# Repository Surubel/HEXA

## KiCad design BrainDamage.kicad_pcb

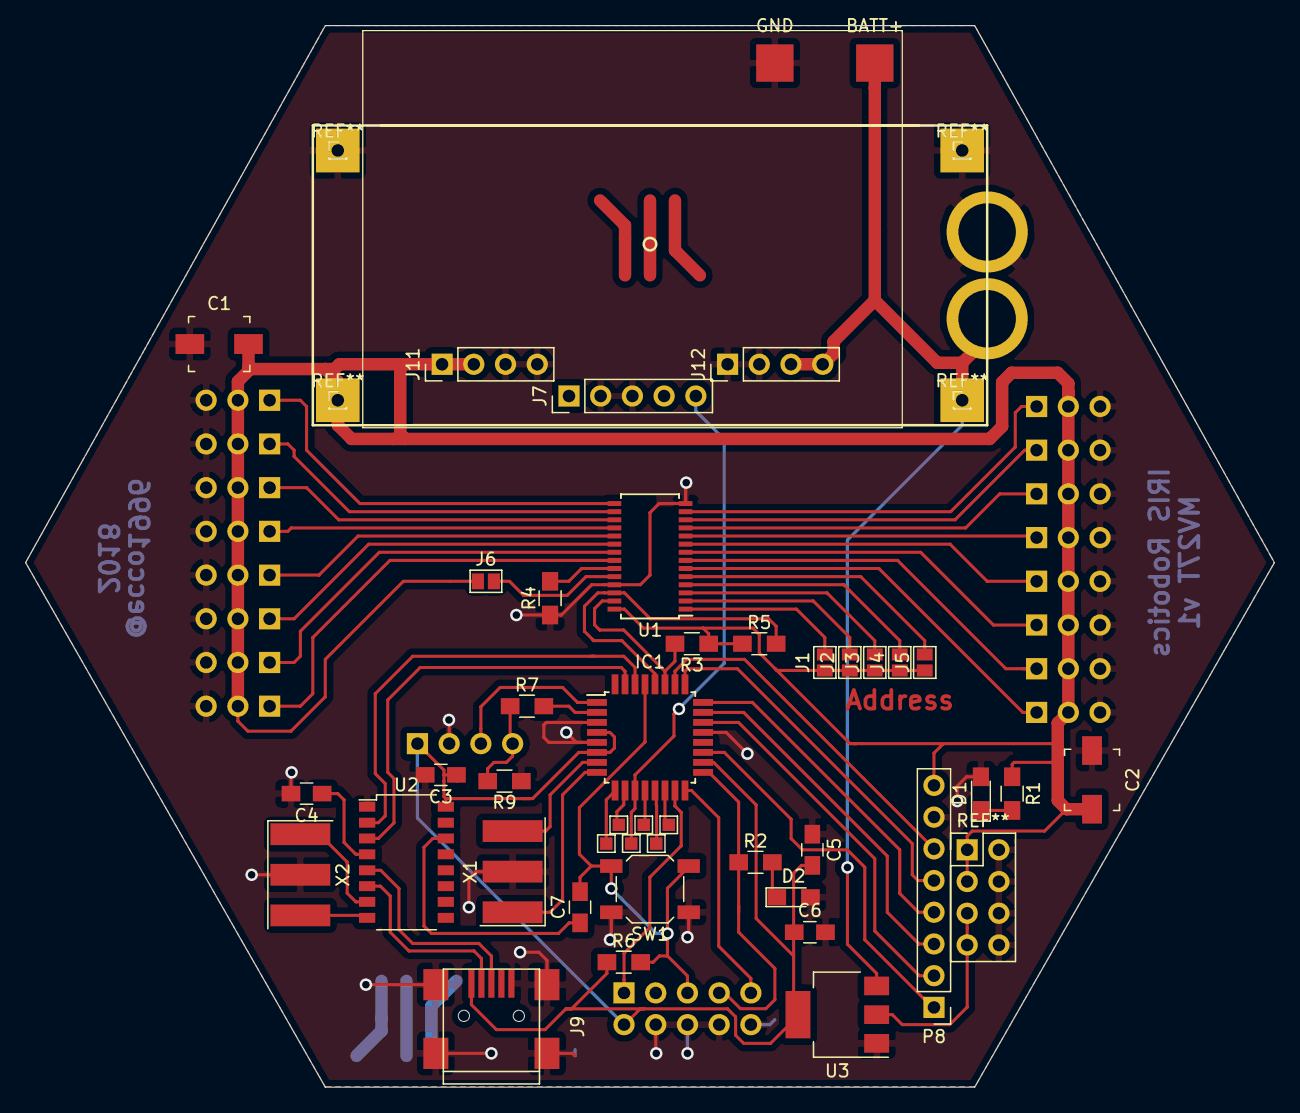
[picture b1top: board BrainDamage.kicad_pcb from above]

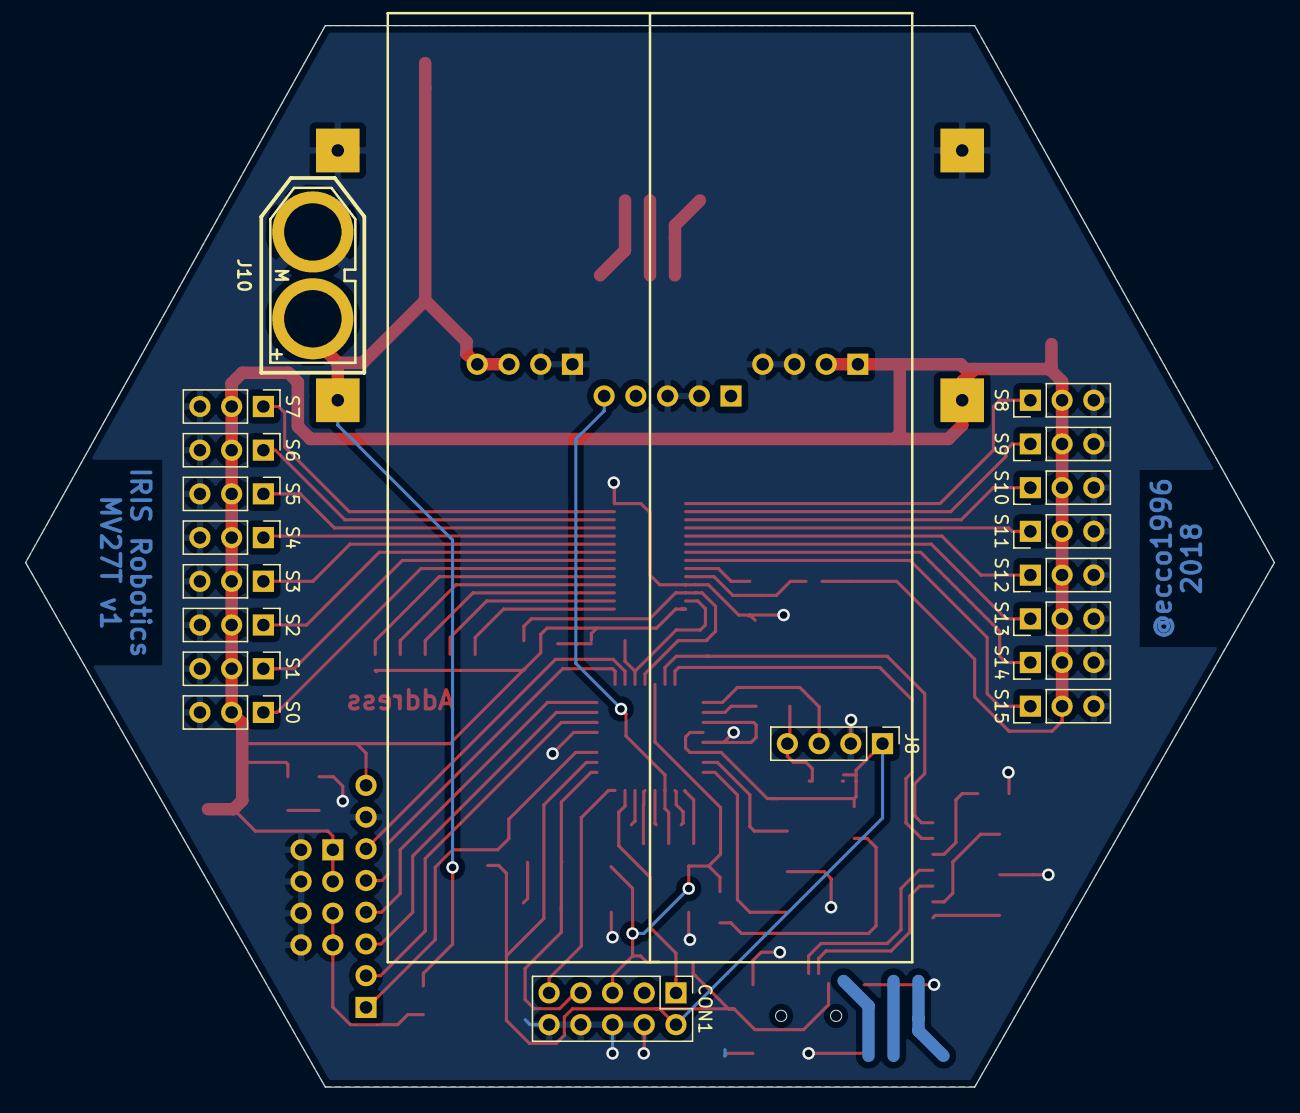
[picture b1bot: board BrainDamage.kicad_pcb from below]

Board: 2 copper layers, 100.0 x 85.0 mm, 56 parts (19 on the bottom side), 54 nets.

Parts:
BATT+: Measurement_Point_Square-SMD-Pad_Big
C1, C2: C; C_Trimmer_Murata_TZB4-A
C3, C6: C; C_0805_HandSoldering
C4, C5, C7: 1n; C_0805_HandSoldering
CON1: AVR-ISP-10; Pin_Header_Straight_2x05_Pitch2.54mm
D1, D2: LED; LED_0805_HandSoldering
GND: Measurement_Point_Square-SMD-Pad_Big
IC1: ATMEGA328P-A; TQFP-32_7x7mm_Pitch0.8mm
J1, J2, J3, J4, J5, J6: TEST_2P; GS2
J7: 15A; Pin_Header_Straight_1x05_Pitch2.54mm
J8: Bluetooth; Pin_Header_Straight_1x04_Pitch2.54mm
J9: USB_OTG; USB_Mini-B
J10: Conn_01x02; XT-60_male
J11, J12: Conn_01x04; Pin_Header_Straight_1x04_Pitch2.54mm
P8: CONN_01X08; Pin_Header_Straight_1x08_Pitch2.54mm
R1, R2: 1K; R_0805_HandSoldering
R3, R4, R5, R6, R9: 10K; R_0805_HandSoldering
R7: 20K; R_0805_HandSoldering
S0, S1, S2, S3, S4, S5, S6, S7, S8, S9, S10, S11, S12, S13, S14, S15: CONN_01X03; Pin_Header_Straight_1x03_Pitch2.54mm
SW1: SW_PUSH; SW_SPST_SKQG
U1: PCA9685-TSSOP; TSSOP-28_4.4x9.7mm_Pitch0.65mm
U2: CH340G; SOP-16_4.4x10.4mm_Pitch1.27mm
U3: AP1117-50; SOT-223-3Lead_TabPin2
X1, X2: CRYSTAL_SMD; Resonator_SMD_muRata_SFSKA-3pin_7.9x3.8mm_HandSoldering

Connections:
+5V: C1.2, C2.2, C3.1, C5.2, C6.1, CON1.2, IC1.4, IC1.6, IC1.18, J1.1, J2.1, J3.1, J4.1, J5.1, J6.1, J8.1, J9.1, J11.1, J11.2, P8.8, R1.1, R3.1, R5.1, R6.1, S0.2, S1.2, S2.2, S3.2, S4.2, S5.2, S6.2, S7.2, S8.2, S9.2, S10.2, S11.2, S12.2, S13.2, S14.2, S15.2, U1.28, U2.16, U3.2
/A0: J1.2, U1.1
/A1: J2.2, U1.2
/A2: J3.2, U1.3
/A3: J4.2, U1.4
/A4: J5.2, U1.5
/A5: J6.2, U1.24
/ADC6: IC1.19, P8.1
/ADC7: IC1.22, P8.2
/BATT+: BATT+.1, J10.2, J12.3, J12.4, U3.3
/LED0: S0.1, U1.6
/LED1: S1.1, U1.7
/LED2: S2.1, U1.8
/LED3: S3.1, U1.9
/LED4: S4.1, U1.10
/LED5: S5.1, U1.11
/LED6: S6.1, U1.12
/LED7: S7.1, U1.13
/LED8: S8.1, U1.15
/LED9: S9.1, U1.16
/LED10: S10.1, U1.17
/LED11: S11.1, U1.18
/LED12: S12.1, U1.19
/LED13: S13.1, U1.20
/LED14: S14.1, U1.21
/LED15: S15.1, U1.22
/MISO: CON1.9, IC1.16
/MOSI: CON1.1, IC1.15
/OE: R4.2, U1.23
/PC0: IC1.23, P8.3
/PC1: IC1.24, P8.4
/PC2: IC1.25, P8.5
/PC3: IC1.26, P8.6
/PG: IC1.11, J7.5
/RESET: C7.2, CON1.5, IC1.29, R6.2, SW1.2
/RX: IC1.30, U2.2
/RXB: IC1.2, R7.2
/SCK: CON1.7, IC1.17, R2.1
/SCL: IC1.28, R5.2, U1.26
/SDA: IC1.27, R3.2, U1.27
/TX: IC1.31, U2.3
/TXB: IC1.1, J8.3
/XTAL1: IC1.7, X1.3
/XTAL2: IC1.8, X1.1
GND: C1.1, C2.1, C3.2, C4.2, C5.1, C6.2, CON1.4, CON1.6, CON1.8, CON1.10, D1.2, D2.2, GND.1, IC1.3, IC1.5, IC1.21, J7.2, J7.3, J8.2, J9.5, J9.6, J10.1, J11.3, J11.4, J12.1, J12.2, P8.7, R4.1, R9.1, S0.3, S1.3, S2.3, S3.3, S4.3, S5.3, S6.3, S7.3, S8.3, S9.3, S10.3, S11.3, S12.3, S13.3, S14.3, S15.3, SW1.1, U1.14, U1.25, U2.1, U3.1, X1.2, X2.2
unnamed: C4.1, U2.4
unnamed: C7.1, U2.14
unnamed: D1.1, R1.2
unnamed: D2.1, R2.2
unnamed: J8.4, R7.1, R9.2
unnamed: J9.2, U2.6
unnamed: J9.3, U2.5
unnamed: U2.7, X2.1
unnamed: U2.8, X2.3
